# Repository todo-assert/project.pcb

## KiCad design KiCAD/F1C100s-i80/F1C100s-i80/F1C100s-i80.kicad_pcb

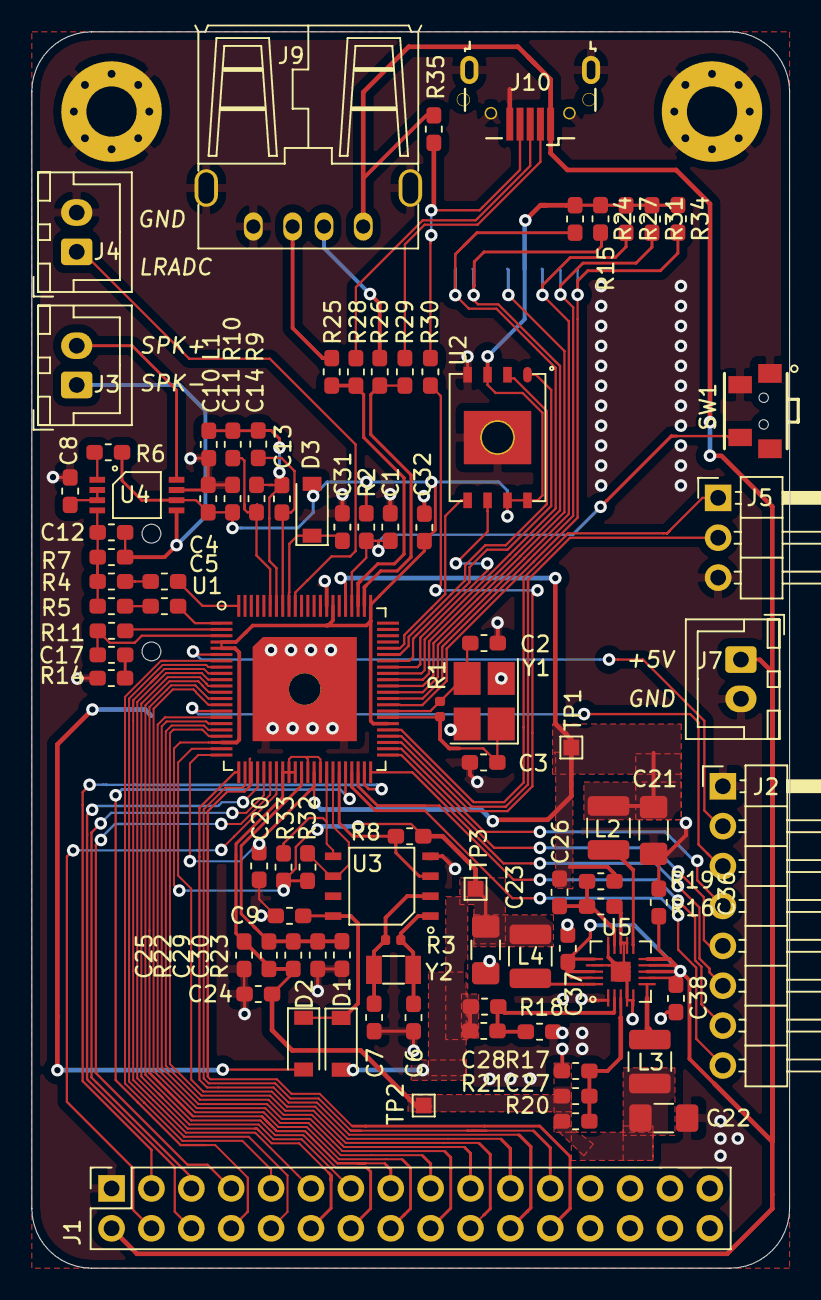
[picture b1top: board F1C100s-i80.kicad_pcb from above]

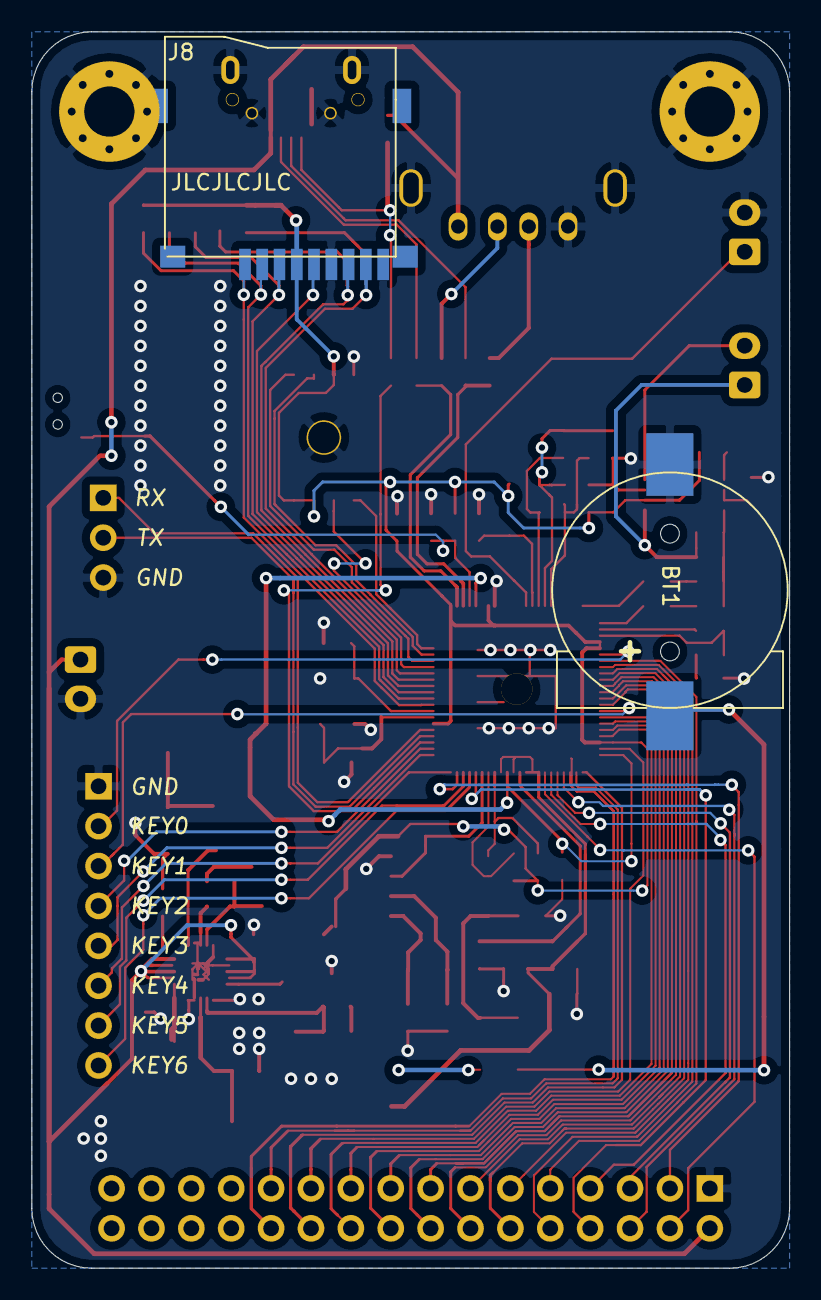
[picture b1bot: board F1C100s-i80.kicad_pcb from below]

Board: 2 copper layers, 48.3 x 78.7 mm, 94 parts (2 on the bottom side), 88 nets.

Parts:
BT1: Battery; CR1220-2
C1: 220pF; C_0603_1608Metric_Pad1.05x0.95mm_HandSolder
C2, C3: 12pF; C_0603_1608Metric_Pad1.05x0.95mm_HandSolder
C4, C5, C8, C9, C11, C13, C14, C20, C24, C25, C31, C32: 1uF; C_0603_1608Metric_Pad1.05x0.95mm_HandSolder
C6, C7: 22pF; C_0603_1608Metric_Pad1.05x0.95mm_HandSolder
C10, C26, C27, C28: 0.1uF; C_0603_1608Metric_Pad1.05x0.95mm_HandSolder
C12: 1nF; C_0603_1608Metric_Pad1.05x0.95mm_HandSolder
C17, C29, C30, C36, C37, C38: 100nF; C_0603_1608Metric_Pad1.05x0.95mm_HandSolder
C21, C22, C23: 10uF; C_1206_3216Metric_Pad1.42x1.75mm_HandSolder
D1, D2, D3: 1N4149; D_SOD-123
J1: LCD_I8080_CONNECTOR_16x2-DIP; PinSocket_2x16_P2.54mm_Vertical
J2: Key Export; PinHeader_1x08_P2.54mm_Horizontal
J3: SPK; JST_XH_B2B-XH-A_1x02_P2.50mm_Vertical
J4: LRADC; JST_XH_B2B-XH-A_1x02_P2.50mm_Vertical
J5: UART; PinHeader_1x03_P2.54mm_Horizontal
J7: Power; JST_XH_B2B-XH-A_1x02_P2.50mm_Vertical
J8: Micro_SD_Card; TF-015
J9: USB_A; USB-AF90
J10: USB_B_Micro; USB_Micro
L1: 2KΩ 100MHz; L_0603_1608Metric_Pad1.05x0.95mm_HandSolder
L2, L3, L4: 1.5uH; L_1210_3225Metric
M3, M3#2: M3; MountingHole_3.2mm_M3_Pad_Via
R1, R3: 1M; R_0402_1005Metric
R2, R8, R32, R33: 4K7; R_0603_1608Metric_Pad1.05x0.95mm_HandSolder
R4, R5, R7: 20K; R_0603_1608Metric_Pad1.05x0.95mm_HandSolder
R6: 10K; R_0603_1608Metric_Pad1.05x0.95mm_HandSolder
R9, R10: 200K; R_0603_1608Metric_Pad1.05x0.95mm_HandSolder
R11, R30, R35: 0R; R_0603_1608Metric_Pad1.05x0.95mm_HandSolder
R14, R25, R26, R28, R29: 22R; R_0603_1608Metric_Pad1.05x0.95mm_HandSolder
R15, R24, R27, R31, R34: 47K; R_0603_1608Metric_Pad1.05x0.95mm_HandSolder
R16, R19, R22, R23: 100K; R_0603_1608Metric_Pad1.05x0.95mm_HandSolder
R17: 150K; R_0603_1608Metric_Pad1.05x0.95mm_HandSolder
R18: 110K; R_0603_1608Metric_Pad1.05x0.95mm_HandSolder
R20, R21: 510K; R_0603_1608Metric_Pad1.05x0.95mm_HandSolder
SW1: SW_Push; SW-Button-TS-018
TP1: +1V2; TestPoint_Pad_1.0x1.0mm
TP2: +2V5; TestPoint_Pad_1.0x1.0mm
TP3: +3V3; TestPoint_Pad_1.0x1.0mm
U1: F1C100S-QFN88; F1C100S-QFN-88_EP_10x10_Pitch0.4mm_Handsoldering
U2: W25Q32JVZP; GD5F1GQ4xBxIG_Handsoldering
U3: PCF8563TS; PCF8563-SO8
U4: LN4990; LN4990E-MSOP-8
U5: EA3036; EA3036-QFN-20_EP_3.55x3.55_Pitch0.4mm
Y1: 24MHz; Crystal_SMD_SeikoEpson_TSX3225-4Pin_3.2x2.5mm_HandSoldering
Y2: 32.768KHz; Crystal_SMD_3215-2Pin_3.2x1.5mm

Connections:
+1V2: C20.1, C21.1, C26.1, L2.1, R19.1, TP1.1, U1.22, U1.35, U1.71
+2V5: C22.1, C24.1, C25.1, C27.1, C29.2, L3.1, R20.1, R22.2, TP2.1, U1.30, U1.31, U1.32, U1.34, U1.36
+3V3: C10.2, C11.2, C23.1, C28.1, C32.1, D1.2, D3.2, J8.4, L4.1, R2.1, R6.1, R8.1, R15.1, R21.1, R24.1, R27.1, R31.1, R32.1, R33.1, R34.1, TP3.1, U1.4, U1.5, U1.20, U1.50, U1.67, U1.73, U2.3, U2.7, U2.8, U4.6
+5V: C36.2, C37.2, C38.2, J1.2, J7.1, J9.1, J10.1, R35.2, U5.7, U5.8, U5.9, U5.10, U5.16, U5.18, U5.19
/AGND: C13.2, C14.2, L1.1, R9.2, R10.2, U1.82
/AVCC: C31.1, D3.1, U1.80
/D+: J9.3, R25.1
/D-: J9.2, R26.1
/DB0: J1.9, U1.7
/DB1: J1.10, U1.8
/DB2: J1.11, U1.9
/DB3: J1.12, U1.10
/DB4: J1.13, U1.11
/DB5: J1.14, U1.12
/DB6: J1.15, U1.13
/DB7: J1.16, U1.14
/DB8: J1.17, U1.16
/DB9: J1.18, U1.17
/DB10: J1.19, U1.18
/DB11: J1.20, U1.19
/DB12: J1.21, U1.21
/DB13: J1.22, U1.23
/DB14: J1.23, U1.24
/DB15: J1.24, U1.25
/HOSCI: C3.2, R1.2, U1.51, Y1.1
/HOSCO: C2.2, R1.1, U1.52, Y1.3
/HPCOM: C17.2, R11.1, U1.3
/HPCOMFB: R11.2, U1.2
/HPL: C5.2, U1.1
/HPR: C4.2, U1.88
/KEY0: J2.2, U1.6
/KEY1: J2.3, U1.15
/KEY2: J2.5, U1.45
/KEY3: J2.6, U1.44
/KEY4: J2.7, U1.42
/KEY5: J2.8, U1.41
/KEYX: J2.4, U1.46
/LCD_BL: J1.3, U1.43
/LCD_CS: J1.4, U1.29
/LCD_RD: J1.7, U1.28
/LCD_RS: J1.5, U1.27
/LCD_RST: J1.8, U1.40
/LCD_WR: J1.6, U1.26
/LRADC: J4.1, U1.79
/RESET: C1.1, R2.2, SW1.4, U1.70
/RTC_INT: R8.2, U1.39, U3.3
/RTC_SCL: R32.2, U1.38, U3.6
/RTC_SDA: R33.2, U1.37, U3.5
/SDC0_CLK: J8.5, U1.56
/SDC0_CMD: J8.3, R27.2, U1.55
/SDC0_D0: J8.7, R24.2, U1.57
/SDC0_D1: J8.8, R15.2, U1.58
/SDC0_D2: J8.1, R34.2, U1.53
/SDC0_D3: J8.2, R31.2, U1.54
/SF_CLK: U1.59, U2.6
/SF_CS: U1.60, U2.1
/SF_MISO: U1.61, U2.2
/SF_MOSI: U1.62, U2.5
/SVREF: C29.1, C30.2, R22.1, R23.2, U1.33
/UART0_RX: J5.1, U1.49
/UART0_TX: J5.2, U1.48
/USB_D+: R25.2, R28.2, U1.69
/USB_D-: R26.2, R29.2, U1.68
/USB_ID: R30.2, U1.47
/VRA1: C13.1, R9.1, U1.81
/VRA2: C14.1, R10.1, U1.83
GND: BT1.2, C1.2, C2.1, C3.1, C6.2, C7.2, C8.2, C9.2, C10.1, C11.1, C20.2, C21.2, C22.2, C23.2, C24.2, C25.2, C30.1, C31.2, C32.2, C36.1, C37.1, C38.1, J1.1, J2.1, J4.2, J5.3, J7.2, J8.6, J8.9, J9.4, J9.5, J10.5, J10.6, L1.2, M3.1, M3#2.1, R14.1, R16.2, R17.2, R18.2, R23.1, SW1.1, SW1.3, U1.74, U1.89, U2.4, U2.9, U3.4, U4.7, U5.1, U5.4, U5.5, U5.12, U5.13, U5.15, U5.17, U5.21, Y1.2, Y1.4
unnamed: BT1.1, D2.2
unnamed: C4.1, R4.1
unnamed: C5.1, R5.1
unnamed: C6.1, R3.1, U3.1, Y2.1
unnamed: C7.1, R3.2, U3.2, Y2.2
unnamed: C8.1, U4.2, U4.3
unnamed: C9.1, D1.1, D2.1, U3.8
unnamed: C12.1, J3.1, R7.2, U4.5
unnamed: C12.2, R4.2, R5.2, R7.1, U4.4
unnamed: C17.1, R14.2
unnamed: C26.2, R16.1, R19.2, U5.14
unnamed: C27.2, R17.1, R20.2, U5.3
unnamed: C28.2, R18.1, R21.2, U5.2
unnamed: J3.2, U4.8
unnamed: J10.2, R29.1
unnamed: J10.3, R28.1
unnamed: J10.4, R30.1, R35.1
unnamed: L2.2, U5.11
unnamed: L3.2, U5.6
unnamed: L4.2, U5.20
unnamed: R6.2, U4.1

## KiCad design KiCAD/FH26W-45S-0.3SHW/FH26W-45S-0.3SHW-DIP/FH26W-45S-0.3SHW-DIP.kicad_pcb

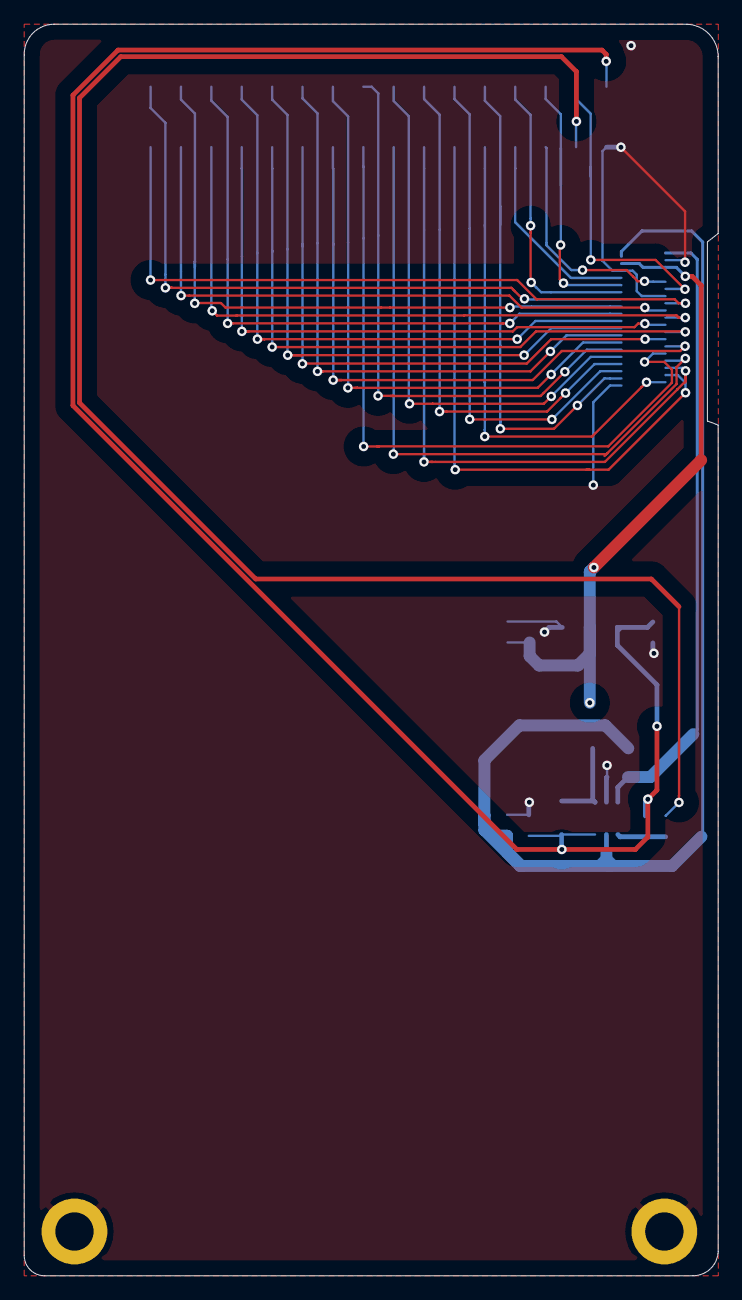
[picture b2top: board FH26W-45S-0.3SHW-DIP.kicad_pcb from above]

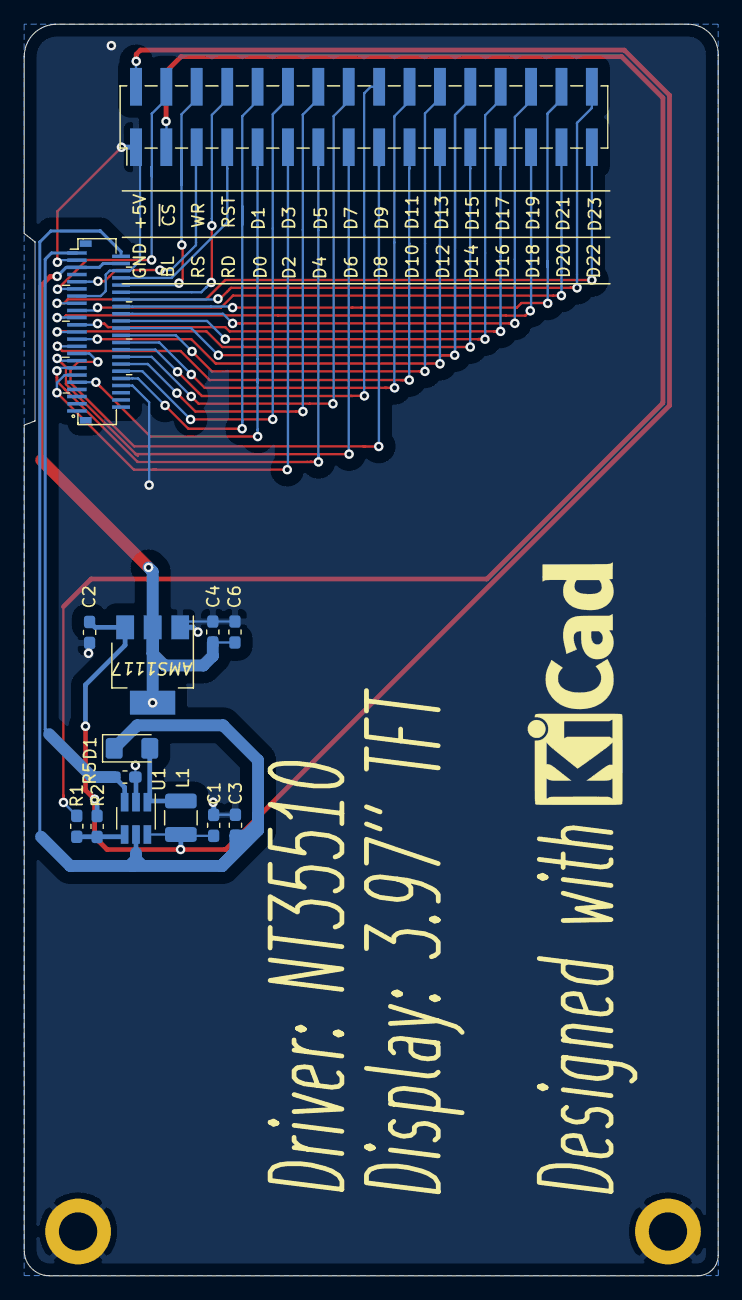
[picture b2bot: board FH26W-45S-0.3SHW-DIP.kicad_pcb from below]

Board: 2 copper layers, 58.0 x 104.6 mm, 16 parts (14 on the bottom side), 37 nets.

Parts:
AMS1117: AMS1117-3.3; SOT-223-3_TabPin2
C1: 10uF; C_0603_1608Metric_Pad1.05x0.95mm_HandSolder
C2: 1uF; C_0603_1608Metric_Pad1.05x0.95mm_HandSolder
C3: 0.1uF/25V; C_0603_1608Metric_Pad1.05x0.95mm_HandSolder
C4, C6: 0.1uF; C_0603_1608Metric_Pad1.05x0.95mm_HandSolder
D1: 1N4148; D_1206_3216Metric_Pad1.42x1.75mm_HandSolder
J1: NT35510-3.97inch-FH26W-45S-0.3SHW(60); NT35510-3.97inch-FH26W-45S-0.3SHW(60)_Handsoldering
J2: LCD_I8080_CONNECTOR_16x2; PinHeader_2x16_P2.54mm_Vertical_SMD
L1: 2.2uH<0.1R/1.5A>; L_1210_3225Metric
R1: 0R; R_0603_1608Metric_Pad1.05x0.95mm_HandSolder
R2: 10K; R_0603_1608Metric_Pad1.05x0.95mm_HandSolder
R5: 5R1; R_0603_1608Metric_Pad1.05x0.95mm_HandSolder
TP9, TP10: M3; MountingHole_3.2mm_M3_ISO14580_Pad
U1: PT4103-SOT23-6; SOT-23-6_Handsoldering

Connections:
+3V3: AMS1117.2, C4.1, C6.1, J1.41, J1.42
+5V: AMS1117.3, C1.1, C2.2, J2.2, L1.1, R2.2, U1.6
/BL: J2.3, R1.2
/DB0: J1.9, J2.9
/DB1: J1.10, J2.10
/DB2: J1.11, J2.11
/DB3: J1.12, J2.12
/DB4: J1.13, J2.13
/DB5: J1.14, J2.14
/DB6: J1.15, J2.15
/DB7: J1.16, J2.16
/DB8: J1.17, J2.17
/DB9: J1.18, J2.18
/DB10: J1.19, J2.19
/DB11: J1.20, J2.20
/DB12: J1.21, J2.21
/DB13: J1.22, J2.22
/DB14: J1.23, J2.23
/DB15: J1.24, J2.24
/DB16: J1.25, J2.25
/DB17: J1.26, J2.26
/DB18: J1.27, J2.27
/DB19: J1.28, J2.28
/DB20: J1.29, J2.29
/DB21: J1.30, J2.30
/DB22: J1.31, J2.31
/DB23: J1.32, J2.32
/LEDA: C3.2, D1.1, J1.44, U1.5
/LEDK: J1.45, R5.2, U1.3
/RD: J1.38, J2.7
/RS: J1.37, J2.5
/RST: J1.34, J2.8
/WR: J1.36, J2.6
/~CS~: J1.35, J2.4
GND: AMS1117.1, C1.2, C2.1, C3.1, C4.2, C6.2, J1.8, J1.33, J1.40, J1.43, J2.1, R5.1, TP9.1, TP10.1, U1.2
unnamed: D1.2, L1.2, U1.1
unnamed: R1.1, R2.1, U1.4

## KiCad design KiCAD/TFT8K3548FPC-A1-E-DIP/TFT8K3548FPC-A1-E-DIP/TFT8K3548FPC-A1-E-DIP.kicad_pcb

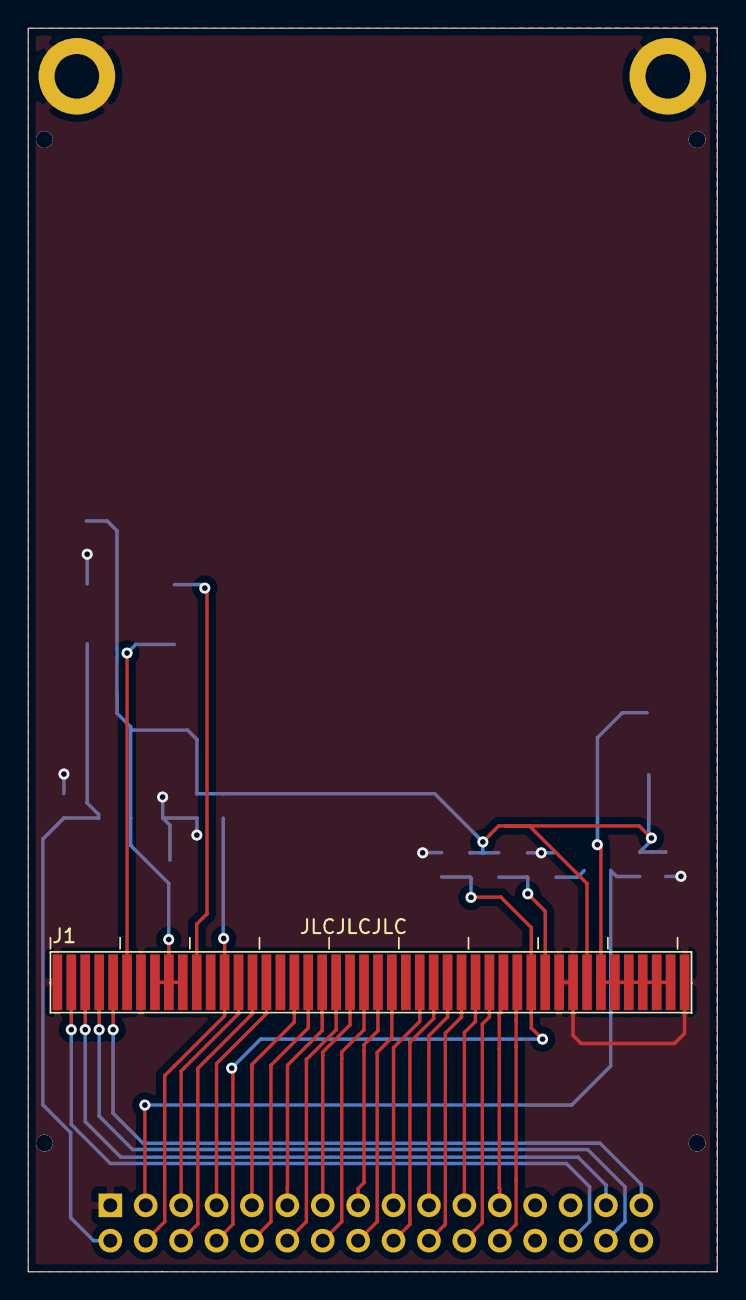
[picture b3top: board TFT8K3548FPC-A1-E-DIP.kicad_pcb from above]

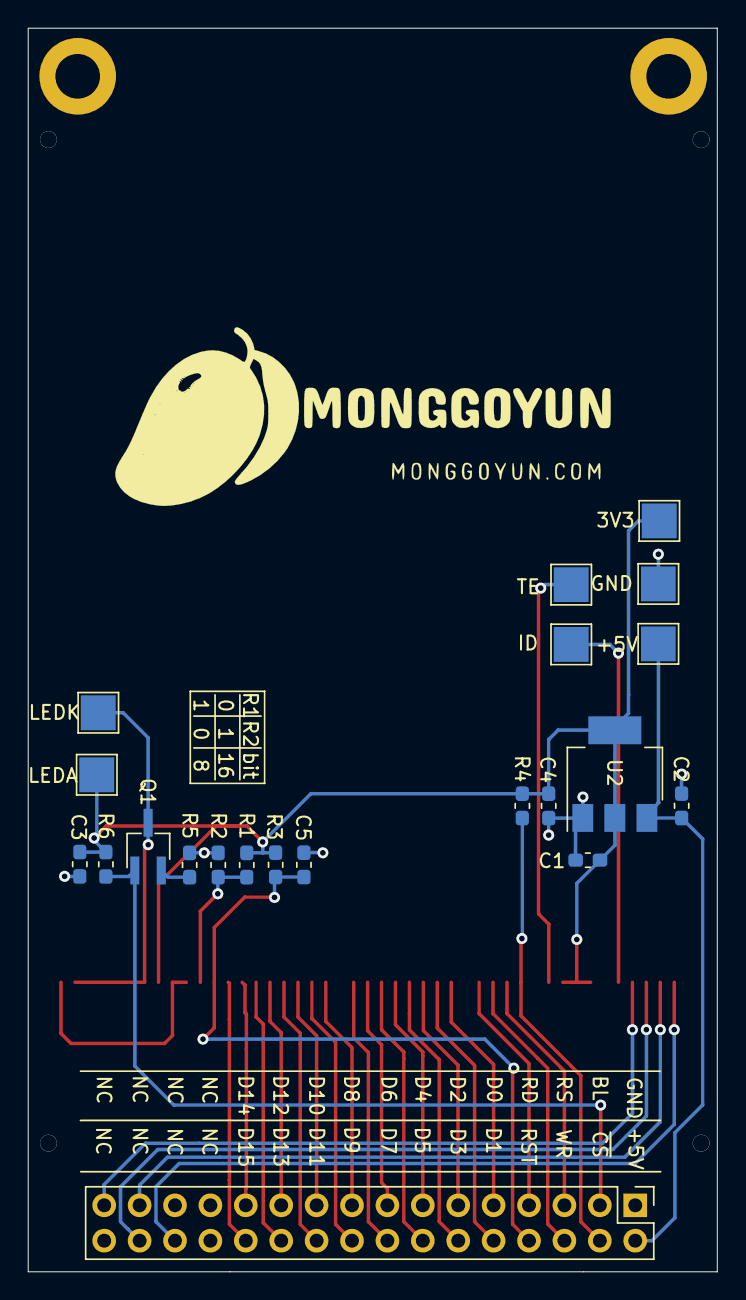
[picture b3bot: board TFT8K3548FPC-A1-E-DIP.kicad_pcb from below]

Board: 2 copper layers, 49.4 x 89.2 mm, 25 parts (22 on the bottom side), 34 nets.

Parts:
3V3: +3.3V; TestPoint_Pad_2.5x2.5mm
+1: LOGO; monggoyun2
+5V: +5V; TestPoint_Pad_2.5x2.5mm
C1, C4: 0.1uF; C_0603_1608Metric_Pad1.05x0.95mm_HandSolder
C2: 1uF; C_0603_1608Metric_Pad1.05x0.95mm_HandSolder
C3: 0.1uF/25F; C_0603_1608Metric_Pad1.05x0.95mm_HandSolder
C5: C; C_0603_1608Metric_Pad1.05x0.95mm_HandSolder
GND: GND; TestPoint_Pad_2.5x2.5mm
ID: LCD_ID; TestPoint_Pad_2.5x2.5mm
J1: TFT8K3548FPC-A1-E
J2: LCD_I8080_CONNECTOR_16x2; PinHeader_2x16_P2.54mm_Vertical
LEDA: LEDA; TestPoint_Pad_2.5x2.5mm
LEDK: LEDK; TestPoint_Pad_2.5x2.5mm
Q1: GP2302; TSOT-23_HandSoldering
R1, R2, R3, R4, R6: 10K; R_0603_1608Metric_Pad1.05x0.95mm_HandSolder
R5: 22R; R_0603_1608Metric_Pad1.05x0.95mm_HandSolder
TE: TE; TestPoint_Pad_2.5x2.5mm
TP8, TP9: M3; MountingHole_3.2mm_M3_ISO14580_Pad
U2: AMS1117-3.3; SOT-223-3_TabPin2

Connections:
+3V3: 3V3.1, C1.2, C3.2, C4.1, J1.8, J1.9, J1.10, J1.39, LEDA.1, R1.2, R3.2, R4.2, R6.2, U2.2
+5V: +5V.1, C2.2, J2.2, U2.3
/BL: J2.3, Q1.1, R6.1
/DB0: J1.18, J2.9
/DB1: J1.19, J2.10
/DB2: J1.20, J2.11
/DB3: J1.21, J2.12
/DB4: J1.22, J2.13
/DB5: J1.23, J2.14
/DB6: J1.24, J2.15
/DB7: J1.25, J2.16
/DB8: J1.27, J2.17
/DB9: J1.28, J2.18
/DB10: J1.29, J2.19
/DB11: J1.30, J2.20
/DB12: J1.31, J2.21
/DB13: J1.32, J2.22
/DB14: J1.33, J2.23
/DB15: J1.34, J2.24
/LCD_ID: ID.1, J1.6
/LEDK: J1.40, J1.41, J1.42, J1.43, J1.44, J1.45, LEDK.1, Q1.3
/RD: J1.16, J2.7
/RS: J1.14, J2.5
/RST: C5.2, J1.35, J2.8, R3.1
/TE: J1.11, TE.1
/WR: J1.15, J2.6
/XL: J1.2, J2.28
/XR: J1.4, J2.30
/YD: J1.5, J2.31
/YU: J1.3, J2.29
/~CS~: J1.13, J2.4, R4.1
GND: C1.1, C2.1, C3.1, C4.2, C5.1, GND.1, J1.1, J1.7, J1.37, J1.38, J1.46, J2.1, R2.1, R5.1, TP8.1, TP9.1, U2.1
unnamed: J1.36, R1.1, R2.2
unnamed: Q1.2, R5.2

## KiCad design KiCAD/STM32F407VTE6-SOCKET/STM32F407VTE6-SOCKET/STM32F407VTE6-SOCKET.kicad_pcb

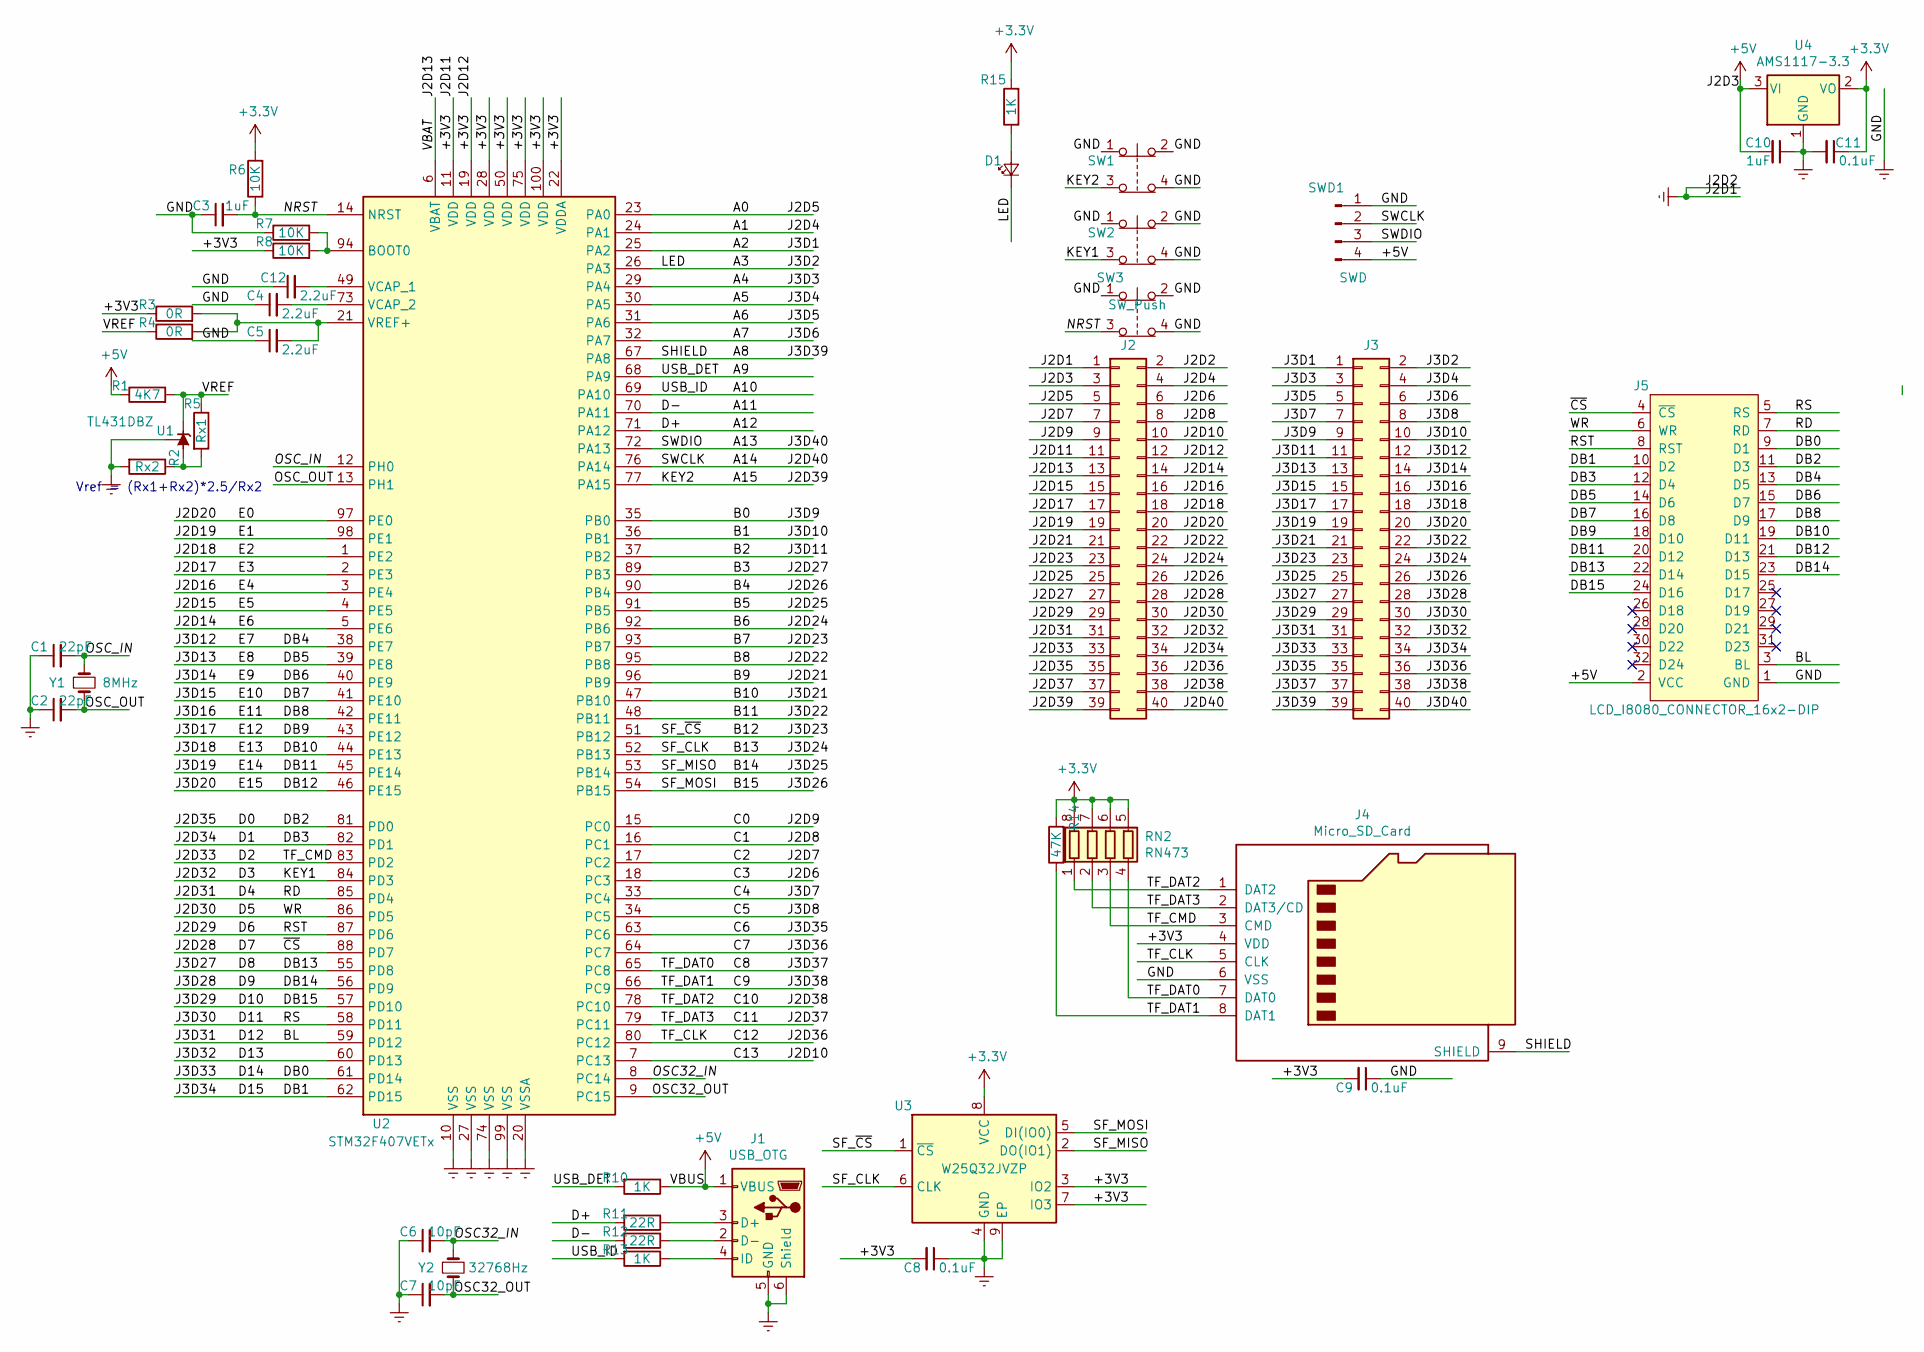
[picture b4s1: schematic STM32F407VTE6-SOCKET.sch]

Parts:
C1, C2: 22pF; C_0402_1005Metric
C3: 1uF; C_0402_1005Metric
C4, C12: 2.2uF; C_0603_1608Metric_Pad1.05x0.95mm_HandSolder
C5: 2.2uF; C_0402_1005Metric
C6, C7: 10pF; C_0402_1005Metric
C8, C9, C11: 0.1uF; C_0603_1608Metric_Pad1.05x0.95mm_HandSolder
C10: 1uF; C_0603_1608Metric_Pad1.05x0.95mm_HandSolder
D1: LED; LED_0805_2012Metric_Pad1.15x1.40mm_HandSolder
J1: USB_OTG; USB_Micro-B_Wuerth_629105150521
J2, J3: Conn_02x20_Odd_Even; PinHeader_2x20_P2.54mm_Vertical
J4: Micro_SD_Card; TF-015
J5: LCD_I8080_CONNECTOR_16x2-DIP; PinSocket_2x16_P2.54mm_Vertical
R1: 4K7; R_0402_1005Metric
R2: Rx2; R_0402_1005Metric
R3, R4: 0R; R_0402_1005Metric
R5: Rx1; R_0402_1005Metric
R6, R7, R8: 10K; R_0402_1005Metric
R10, R13, R15: 1K; R_0603_1608Metric_Pad1.05x0.95mm_HandSolder
R11, R12: 22R; R_0603_1608Metric_Pad1.05x0.95mm_HandSolder
R14: 47K; R_0603_1608Metric_Pad1.05x0.95mm_HandSolder
RN2: RN473; R_Cat16-4
SW1, SW2: SW_MEC_5G; SW-Button-TS-018
SW3: SW_Push; SW-Button-TS-018
SWD1: SWD; PinHeader_1x04_P2.54mm_Horizontal
U1: TL431DBZ; SOT-23
U2: STM32F407VETx; LQFP-100_14x14mm_P0.5mm
U3: W25Q32JVZP; GD5F1GQ4xBxIG_Handsoldering
U4: AMS1117-3.3; SOT-223-3_TabPin2
Y1: 8MHz; Crystal_SMD_5032-2Pin_5.0x3.2mm
Y2: 32768Hz; Crystal_SMD_3215-2Pin_3.2x1.5mm

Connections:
+5V: C10.2, J1.1 (VBUS), J2.3, J5.2 (VCC), R1.1, R10.1, SWD1.4, U4.3 (VI)
/A0: J2.5, U2.23 (PA0)
/A1: J2.4, U2.24 (PA1)
/A2: J3.1, U2.25 (PA2)
/A3: D1.1 (K), J3.2, U2.26 (PA3)
/A4: J3.3, U2.29 (PA4)
/A5: J3.4, U2.30 (PA5)
/A6: J3.5, U2.31 (PA6)
/A7: J3.6, U2.32 (PA7)
/A8: J3.39, J4.9 (SHIELD), U2.67 (PA8)
/A9: R10.2, U2.68 (PA9)
/A10: R13.2, U2.69 (PA10)
/A11: R12.2, U2.70 (PA11)
/A12: R11.2, U2.71 (PA12)
/A13: J3.40, SWD1.3, U2.72 (PA13)
/A14: J2.40, SWD1.2, U2.76 (PA14)
/A15: J2.39, SW1.3, U2.77 (PA15)
/B0: J3.9, U2.35 (PB0)
/B1: J3.10, U2.36 (PB1)
/B2: J3.11, U2.37 (PB2)
/B3: J2.27, U2.89 (PB3)
/B4: J2.26, U2.90 (PB4)
/B5: J2.25, U2.91 (PB5)
/B6: J2.24, U2.92 (PB6)
/B7: J2.23, U2.93 (PB7)
/B8: J2.22, U2.95 (PB8)
/B9: J2.21, U2.96 (PB9)
/B10: J3.21, U2.47 (PB10)
/B11: J3.22, U2.48 (PB11)
/B12: J3.23, U2.51 (PB12), U3.1 (~CS)
/B13: J3.24, U2.52 (PB13), U3.6 (CLK)
/B14: J3.25, U2.53 (PB14), U3.2 (DO(IO1))
/B15: J3.26, U2.54 (PB15), U3.5 (DI(IO0))
/BL: J3.31, J5.3 (BL), U2.59 (PD12)
/C0: J2.9, U2.15 (PC0)
/C1: J2.8, U2.16 (PC1)
/C2: J2.7, U2.17 (PC2)
/C3: J2.6, U2.18 (PC3)
/C4: J3.7, U2.33 (PC4)
/C5: J3.8, U2.34 (PC5)
/C6: J3.35, U2.63 (PC6)
/C7: J3.36, U2.64 (PC7)
/C8: J3.37, J4.7 (DAT0), RN2.4 (R4.1), U2.65 (PC8)
/C9: J3.38, J4.8 (DAT1), R14.1, U2.66 (PC9)
/C10: J2.38, J4.1 (DAT2), RN2.1 (R1.1), U2.78 (PC10)
/C11: J2.37, J4.2 (DAT3/CD), RN2.2 (R2.1), U2.79 (PC11)
/C12: J2.36, J4.5 (CLK), U2.80 (PC12)
/C13: J2.10, U2.7 (PC13)
/D0: J2.35, J5.11 (D3), U2.81 (PD0)
/D1: J2.34, J5.12 (D4), U2.82 (PD1)
/D2: J2.33, J4.3 (CMD), RN2.3 (R3.1), U2.83 (PD2)
/D3: J2.32, SW2.3, U2.84 (PD3)
/D4: J2.31, J5.7 (RD), U2.85 (PD4)
/D5: J2.30, J5.6 (WR), U2.86 (PD5)
/D6: J2.29, J5.8 (RST), U2.87 (PD6)
/D7: J2.28, J5.4 (~CS~), U2.88 (PD7)
/D8: J3.27, J5.22 (D14), U2.55 (PD8)
/D9: J3.28, J5.23 (D15), U2.56 (PD9)
/D10: J3.29, J5.24 (D16), U2.57 (PD10)
/D11: J3.30, J5.5 (RS), U2.58 (PD11)
/D13: J3.32, U2.60 (PD13)
/D14: J3.33, J5.9 (D1), U2.61 (PD14)
/D15: J3.34, J5.10 (D2), U2.62 (PD15)
/DB4: J3.12, J5.13 (D5), U2.38 (PE7)
/DB5: J3.13, J5.14 (D6), U2.39 (PE8)
/DB6: J3.14, J5.15 (D7), U2.40 (PE9)
/DB7: J3.15, J5.16 (D8), U2.41 (PE10)
/DB8: J3.16, J5.17 (D9), U2.42 (PE11)
/DB9: J3.17, J5.18 (D10), U2.43 (PE12)
/DB10: J3.18, J5.19 (D11), U2.44 (PE13)
/DB11: J3.19, J5.20 (D12), U2.45 (PE14)
/DB12: J3.20, J5.21 (D13), U2.46 (PE15)
/E0: J2.20, U2.97 (PE0)
/E1: J2.19, U2.98 (PE1)
/E2: J2.18, U2.1 (PE2)
/E3: J2.17, U2.2 (PE3)
/E4: J2.16, U2.3 (PE4)
/E5: J2.15, U2.4 (PE5)
/E6: J2.14, U2.5 (PE6)
/J2D13: J2.13, U2.6 (VBAT)
/NRST: C3.2, R6.1, SW3.3, U2.14 (NRST)
/OSC32_IN: C6.2, U2.8 (PC14), Y2.1
/OSC32_OUT: C7.2, U2.9 (PC15), Y2.2
/OSC_IN: C1.2, U2.12 (PH0), Y1.1
/OSC_OUT: C2.2, U2.13 (PH1), Y1.2
/VREF: R1.2, R4.1, R5.1, U1.1 (K)
GNDREF: C1.1, C2.1, C3.1, C4.1, C5.1, C6.1, C7.1, C8.1, C9.1, C10.1, C11.2, C12.1, J1.5 (GND), J1.6 (Shield), J2.1, J2.2, J4.6 (VSS), J5.1 (GND), R2.2, R7.1, SW1.1, SW1.2, SW1.4, SW2.1, SW2.2, SW2.4, SW3.1, SW3.2, SW3.4, SWD1.1, U1.2 (REF), U2.10 (VSS), U2.20 (VSSA), U2.27 (VSS), U2.74 (VSS), U2.99 (VSS), U3.4 (GND), U3.9 (EP), U4.1 (GND)
unnamed: C4.2, U2.73 (VCAP_2)
unnamed: C5.2, R3.2, R4.2, U2.21 (VREF+)
unnamed: C12.2, U2.49 (VCAP_1)
unnamed: D1.2 (A), R15.1
unnamed: J1.2 (D-), R12.1
unnamed: J1.3 (D+), R11.1
unnamed: J1.4 (ID), R13.1
unnamed: R2.1, R5.2, U1.3 (A)
unnamed: R7.2, R8.2, U2.94 (BOOT0)

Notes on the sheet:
Vref = (Rx1+Rx2)*2.5/Rx2

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
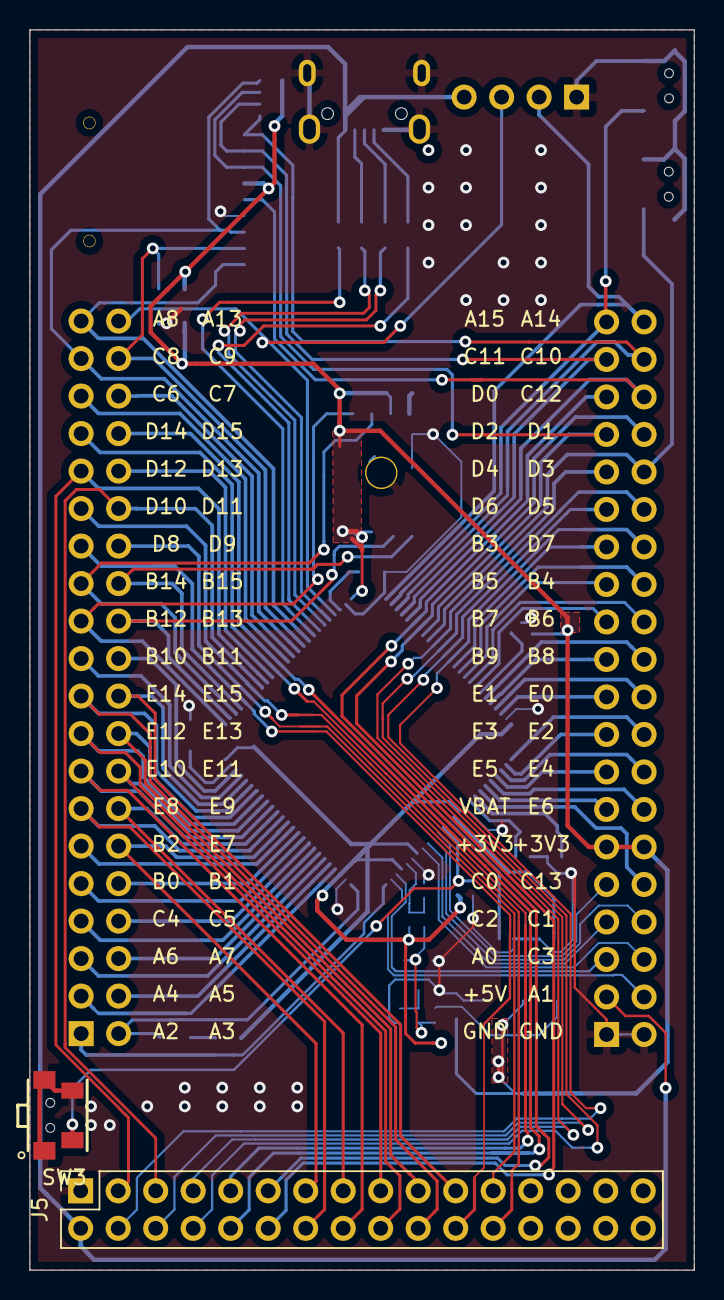
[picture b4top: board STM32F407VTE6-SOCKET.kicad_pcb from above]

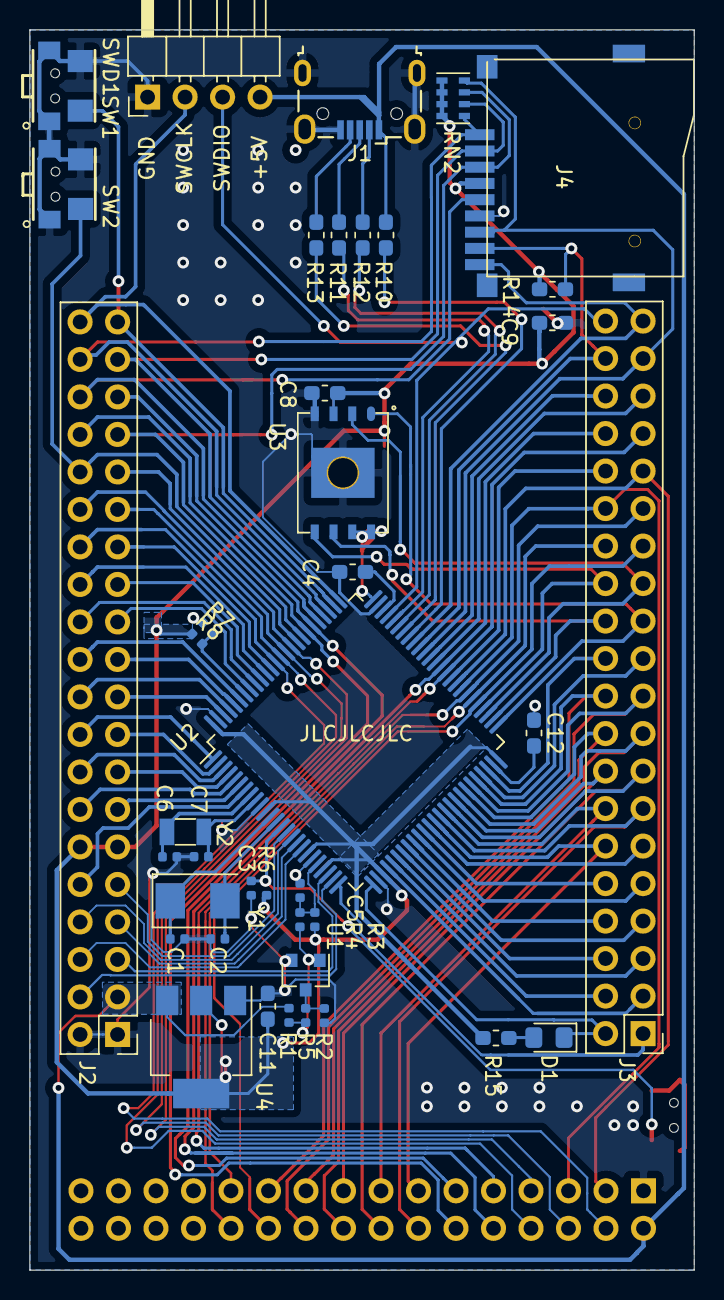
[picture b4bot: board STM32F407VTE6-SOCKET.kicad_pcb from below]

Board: 2 copper layers, 45.0 x 84.0 mm, 42 parts (40 on the bottom side), 97 nets.

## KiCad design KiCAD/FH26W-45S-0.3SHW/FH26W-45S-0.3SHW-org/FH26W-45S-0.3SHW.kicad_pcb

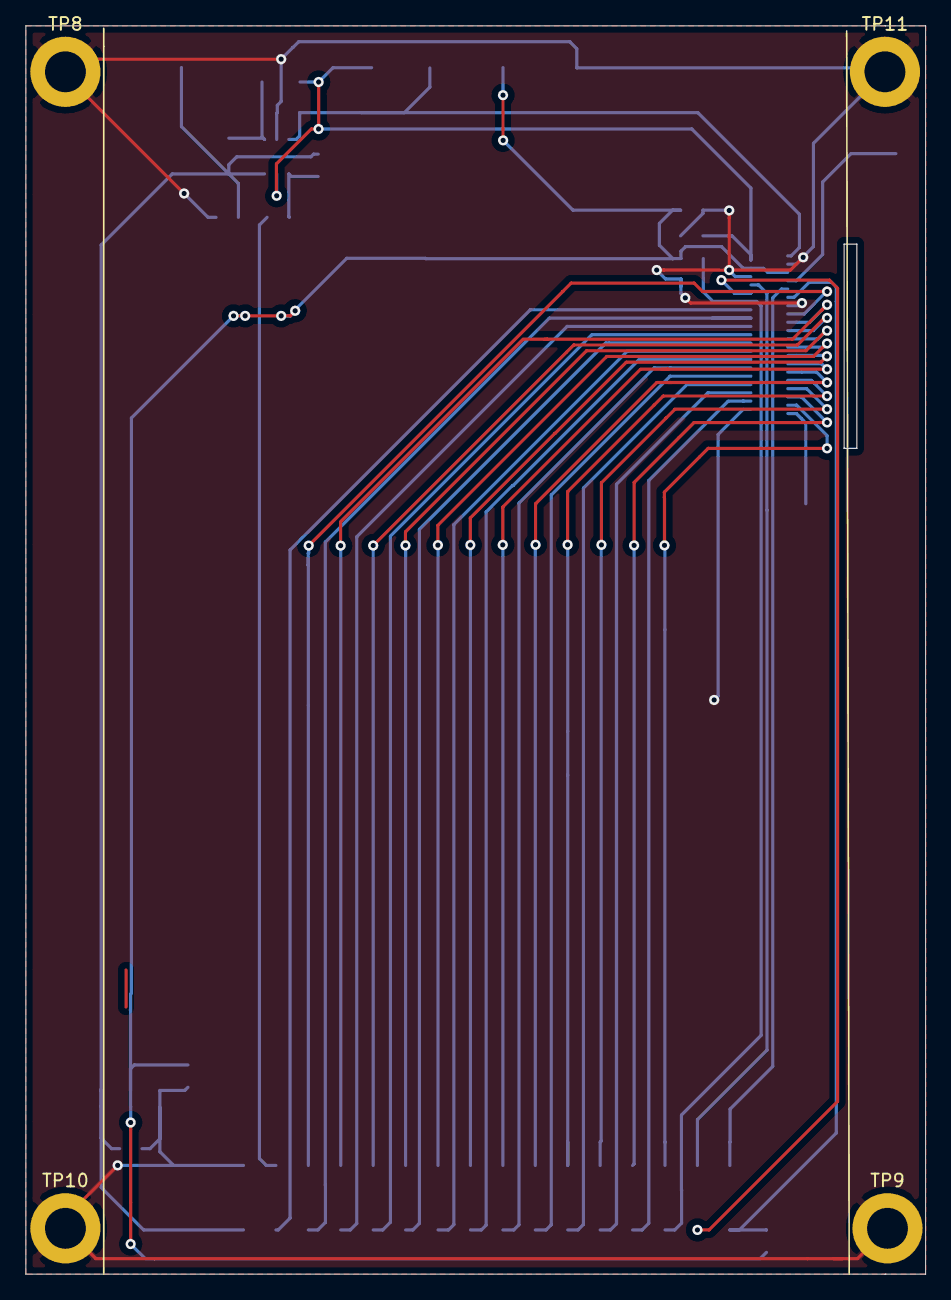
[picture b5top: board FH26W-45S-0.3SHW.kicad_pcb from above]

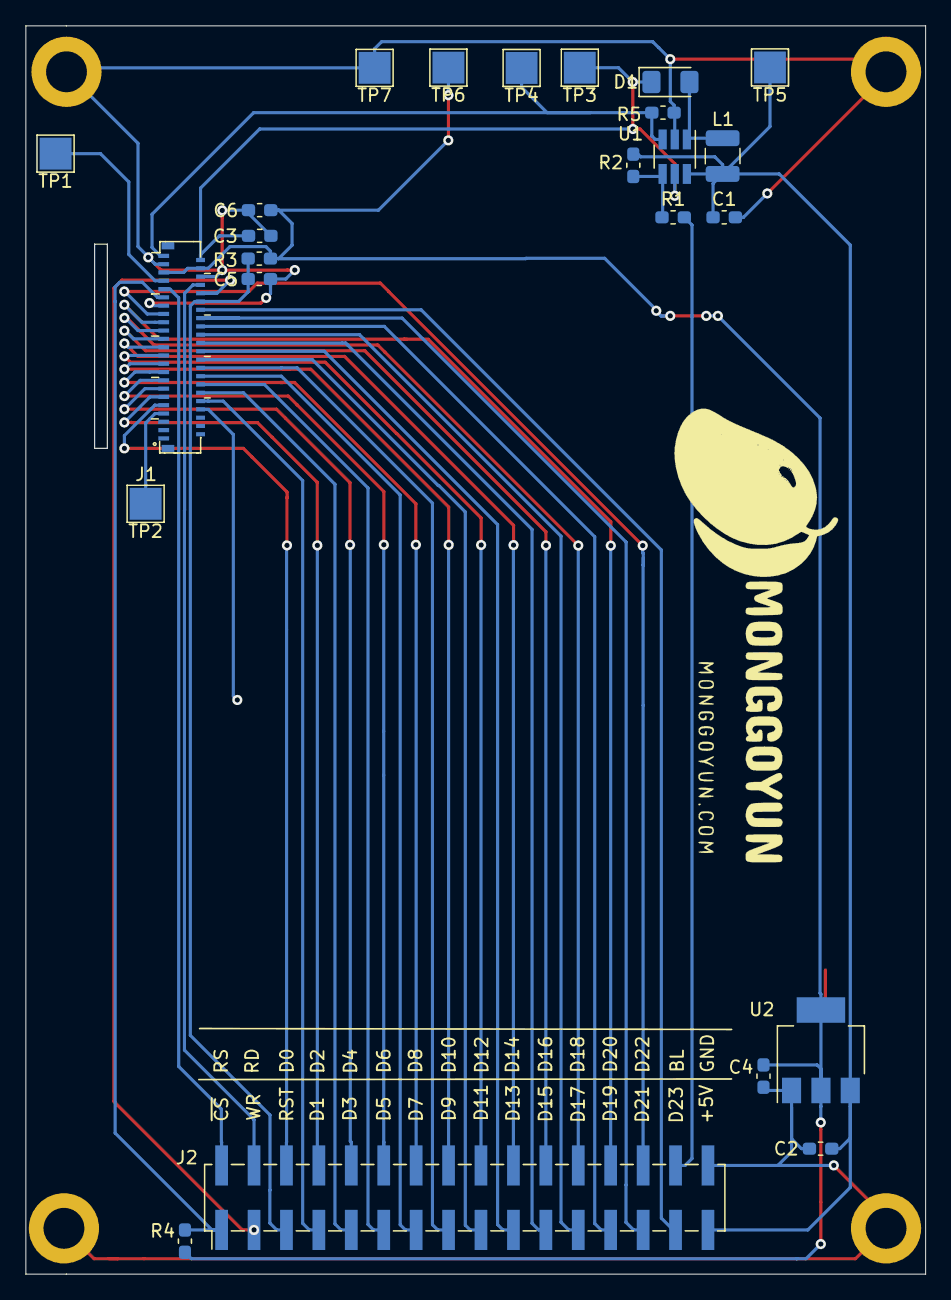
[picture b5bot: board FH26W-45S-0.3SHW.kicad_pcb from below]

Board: 2 copper layers, 70.4 x 97.7 mm, 28 parts (24 on the bottom side), 39 nets.

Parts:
C1: 10uF; C_0603_1608Metric_Pad1.05x0.95mm_HandSolder
C2: 1uF; C_0603_1608Metric_Pad1.05x0.95mm_HandSolder
C3: 0.1uF/25F; C_0603_1608Metric_Pad1.05x0.95mm_HandSolder
C4, C6: 0.1uF; C_0603_1608Metric_Pad1.05x0.95mm_HandSolder
C5: C; C_0603_1608Metric_Pad1.05x0.95mm_HandSolder
D1: 1N4148; D_1206_3216Metric_Pad1.42x1.75mm_HandSolder
J1: NT35510-3.97inch-FH26W-45S-0.3SHW(60)
J2: LCD_I8080_CONNECTOR_16x2; PinHeader_2x16_P2.54mm_Vertical_SMD
L1: 2.2uH<0.1R/1.5A>; L_1210_3225Metric
R1: 0R; R_0603_1608Metric_Pad1.05x0.95mm_HandSolder
R2, R3, R4: 10K; R_0603_1608Metric_Pad1.05x0.95mm_HandSolder
R5: 5R1; R_0603_1608Metric_Pad1.05x0.95mm_HandSolder
TP1: TE; TestPoint_Pad_2.5x2.5mm
TP2: LCD_ID; TestPoint_Pad_2.5x2.5mm
TP3: LEDA; TestPoint_Pad_2.5x2.5mm
TP4: LEDK; TestPoint_Pad_2.5x2.5mm
TP5: +5V; TestPoint_Pad_2.5x2.5mm
TP6: +3.3V; TestPoint_Pad_2.5x2.5mm
TP7: GND; TestPoint_Pad_2.5x2.5mm
TP8, TP9, TP10, TP11: M3; MountingHole_3.2mm_M3_ISO14580_Pad
U1: PT4103-SOT23-6; SOT-23-6_Handsoldering
U2: AMS1117-3.3; SOT-223-3_TabPin2

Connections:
+3V3: C4.1, C6.1, J1.41, J1.42, R3.2, R4.2, TP6.1, U2.2
+5V: C1.1, C2.2, J2.31, L1.1, R2.2, TP5.1, U1.6, U2.3
/BL: J2.30, R1.2
/DB0: J1.9, J2.6
/DB1: J1.10, J2.7
/DB2: J1.11, J2.8
/DB3: J1.12, J2.9
/DB4: J1.13, J2.10
/DB5: J1.14, J2.11
/DB6: J1.15, J2.12
/DB7: J1.16, J2.13
/DB8: J1.17, J2.14
/DB9: J1.18, J2.15
/DB10: J1.19, J2.16
/DB11: J1.20, J2.17
/DB12: J1.21, J2.18
/DB13: J1.22, J2.19
/DB14: J1.23, J2.20
/DB15: J1.24, J2.21
/DB16: J1.25, J2.22
/DB17: J1.26, J2.23
/DB18: J1.27, J2.24
/DB19: J1.28, J2.25
/DB20: J1.29, J2.26
/DB21: J1.30, J2.27
/DB22: J1.31, J2.28
/DB23: J1.32, J2.29
/LCD_ID: J1.7, TP2.1
/LEDA: C3.2, D1.1, J1.44, TP3.1, U1.5
/LEDK: J1.45, R5.2, TP4.1, U1.3
/RD: J1.38, J2.4
/RS: J1.37, J2.2
/RST: C5.2, J1.34, J2.5, R3.1
/TE: J1.39, TP1.1
/WR: J1.36, J2.3
/~CS~: J1.35, J2.1, R4.1
GND: C1.2, C2.1, C3.1, C4.2, C5.1, C6.2, J1.8, J1.33, J1.40, J1.43, J2.32, R5.1, TP7.1, TP8.1, TP9.1, TP10.1, TP11.1, U1.2, U2.1
unnamed: D1.2, L1.2, U1.1
unnamed: R1.1, R2.1, U1.4

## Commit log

2019-05-26 f1c100s clock & photo player
2019-05-27 add datasheet about IC
2019-05-28 complete rtc & audio
2019-05-29 finished
    Schematic finished
2019-06-01 add datasheet
2019-06-04 modify
2019-06-11 place off-page
2019-06-11 create netlist
2019-06-12 replace sw & recreate netlist
2019-06-13 create board
2019-06-13 update xps
2019-06-16 layout
2019-06-24 DATASHEET
2019-06-25 N32926 OB
2019-06-26 ADD FLASH
2019-06-26 USB PART1
2019-07-25 save
2019-08-08 okay
2019-08-27 32926
2019-09-17 other
2019-10-31 32926 tiny
2019-11-19 aaaa
2019-11-24 LCD_board
2019-11-27 OK 3.94 LCD
2019-12-28 C100S
2020-03-11 c100s&f40x
2020-03-22 add DS stm32f401ccu6
2020-04-12 add auto
2020-04-15 添加DS并完善原理图
2020-05-14 增加DS
2020-05-14 添加cd4052 DS
2020-11-16 修改DCDC部分
2020-12-17 更改C100s走线
2020-12-17 添加MS8412 DS
2021-02-03 修改排阻为0603电阻
